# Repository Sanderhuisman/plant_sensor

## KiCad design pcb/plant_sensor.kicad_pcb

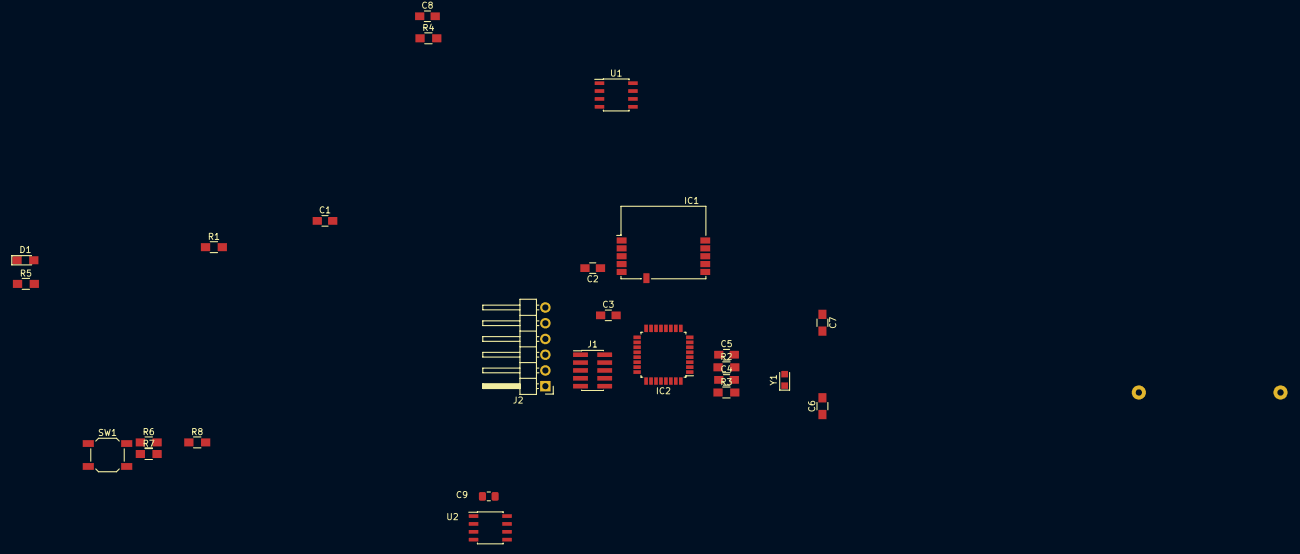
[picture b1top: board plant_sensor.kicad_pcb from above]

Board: 2 copper layers, 27 parts (1 on the bottom side), 20 nets, no tracks yet.

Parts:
BT1: CR2032; CR2032H
C1: 1uF X5R; C_0805_HandSoldering
C2: 1uF; C_0805_HandSoldering
C3, C4, C5, C8: 100nF; C_0805_HandSoldering
C6, C7: 4.3pF; R_0805_HandSoldering
C9: 100nF; C_0805_2012Metric_Pad1.15x1.40mm_HandSolder
D1: RED; LED_0805_HandSoldering
IC1: SPBTLE-RF0; ST_SPBTLE
IC2: STM32L052K8Tx; LQFP-32_7x7mm_Pitch0.8mm
J1: Conn_ARM_JTAG_SWD_10; Pin_Header_Straight_2x05_Pitch1.27mm_SMD
J2: COM; Pin_Header_Angled_1x06_Pitch2.54mm
R1: 47K; R_0805_HandSoldering
R2: FBead; R_0805_HandSoldering
R3, R4, R8: 10K; R_0805_HandSoldering
R5: 1K; R_0805_HandSoldering
R6, R7: 4K7; R_0805_HandSoldering
SW1: SW_Push; SW_SPST_SKQG
U1: M95256-WMN6P; SOIC-8_3.9x4.9mm_Pitch1.27mm
U2: LM75B; SOIC-8_3.9x4.9mm_P1.27mm
Y1: 32.768kHz; Crystal_SMD_TXC_9HT11-2pin_2.0x1.2mm_HandSoldering

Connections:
+3V3: C2.1, C3.1, C4.1, C9.1, IC1.5, IC2.1, IC2.17, J1.1, R2.1, R4.1, R8.1, U2.8
+BATT: BT1.1, C1.1
/BLE/BLE_IRQ: IC1.4, R1.1
/MCU/I2C1_SCL: IC2.29, R6.2, U2.1
/MCU/I2C1_SDA: IC2.30, R7.2, U2.2
/MCU/RCC_OSC32_IN: C6.1, IC2.2, Y1.1
/MCU/RCC_OSC32_OUT: C7.1, IC2.3, Y1.2
/MCU/RXD: IC2.19, J2.5
/MCU/SPI1_CLK: IC1.7, IC2.11
/MCU/SPI1_MISO: IC1.8, IC2.12
/MCU/SPI1_MOSI: IC1.9, IC2.13
/MCU/SYS_SWCLK: IC2.24, J1.4
/MCU/SYS_SWDIO: IC2.23, J1.2
/MCU/TEMP_IRQ: IC2.28, R8.2, U2.3
/MCU/TXD: IC2.20, J2.4
/MCU/nRESET: C8.1, IC2.4, J1.10, R4.2, SW1.1
GND: BT1.2, C1.2, C2.2, C3.2, C4.2, C5.2, C6.2, C7.2, C8.2, C9.2, D1.1, IC1.6, IC2.16, IC2.32, J1.3, J1.5, J1.9, J2.1, R1.2, R3.2, SW1.2, U2.4, U2.5, U2.6, U2.7
unnamed: D1.2, R5.2
unnamed: IC2.31, R3.1
VDDA: C5.1, IC2.5, R2.2, R6.1, R7.1

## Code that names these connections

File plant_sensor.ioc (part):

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Mcu.Name=STM32L052K(6-8)Tx
Mcu.Package=LQFP32
Mcu.UserName=STM32L052K8Tx
PA0.Mode=IN0
PA0.Signal=ADC_IN0
PA1.GPIOParameters=GPIO_Label
PA1.GPIO_Label=CHARGE
PA1.Signal=GPIO_Input
PA10.Mode=Asynchronous
PA10.Signal=USART1_RX
PA11.Mode=Device
PA11.Signal=USB_DM
PA12.Mode=Device
PA12.Signal=USB_DP
PA13.Mode=Serial_Wire
PA13.Signal=SYS_SWDIO
PA14.Mode=Serial_Wire
PA14.Signal=SYS_SWCLK
PA4.GPIOParameters=GPIO_Label
PA4.GPIO_Label=LED
PA4.Signal=GPIO_Output
PA5.Mode=Full_Duplex_Master
PA5.Signal=SPI1_SCK
PA6.Mode=Full_Duplex_Master
PA6.Signal=SPI1_MISO
PA7.Mode=Full_Duplex_Master
PA7.Signal=SPI1_MOSI
PA8.GPIOParameters=GPIO_Label
PA8.GPIO_Label=SPI_BLE_RESET
PA8.Signal=GPIO_Output
PA9.Mode=Asynchronous
PA9.Signal=USART1_TX
PB0.GPIOParameters=GPIO_Label
PB0.GPIO_Label=SPI_BLE_IRQ
PB0.Signal=GPXTI0
PB1.GPIOParameters=GPIO_Label
PB1.GPIO_Label=SPI_BLE_CS
PB1.Signal=GPIO_Output
PB3.Mode=G5_IO1-Sampling
PB3.Signal=TSC_G5_IO1
PB4.Mode=G5_IO2-Channel
PB4.Signal=TSC_G5_IO2
PB6.Mode=I2C
PB6.Signal=I2C1_SCL
PB7.Mode=I2C
PB7.Signal=I2C1_SDA
PC14-OSC32_IN.Mode=LSE-External-Oscillator
PC14-OSC32_IN.Signal=RCC_OSC32_IN
PC15-OSC32_OUT.Mode=LSE-External-Oscillator
PC15-OSC32_OUT.Signal=RCC_OSC32_OUT
RCC.SYSCLKFreq_VALUE=32000000
RCC.SYSCLKSource=RCC_SYSCLKSOURCE_PLLCLK
board=custom

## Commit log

2019-03-02 Added i2c moisture sensor repo
2019-03-02 Added stemma
2019-11-03 eagle
2019-11-04 layouting
2019-11-04 Added chirp project
